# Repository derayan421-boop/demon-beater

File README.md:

# demon-beater
My first hackclub project using KiCad and Fusion360

BOM:
- 3x Cherry MX Switches
- 3x Blank DSA Keycaps
- 1x XIAO RP2040
- 1x SK6812 MINI Led
- 4x M3x16 Bolt
- 4x M3 Heatset

Others(?):
- KMK Firmware
- Top Case.stl
- Bottom Case.stl

Schematic   |   PCB   | Case
:---:|:---:|:---:|
   |      |

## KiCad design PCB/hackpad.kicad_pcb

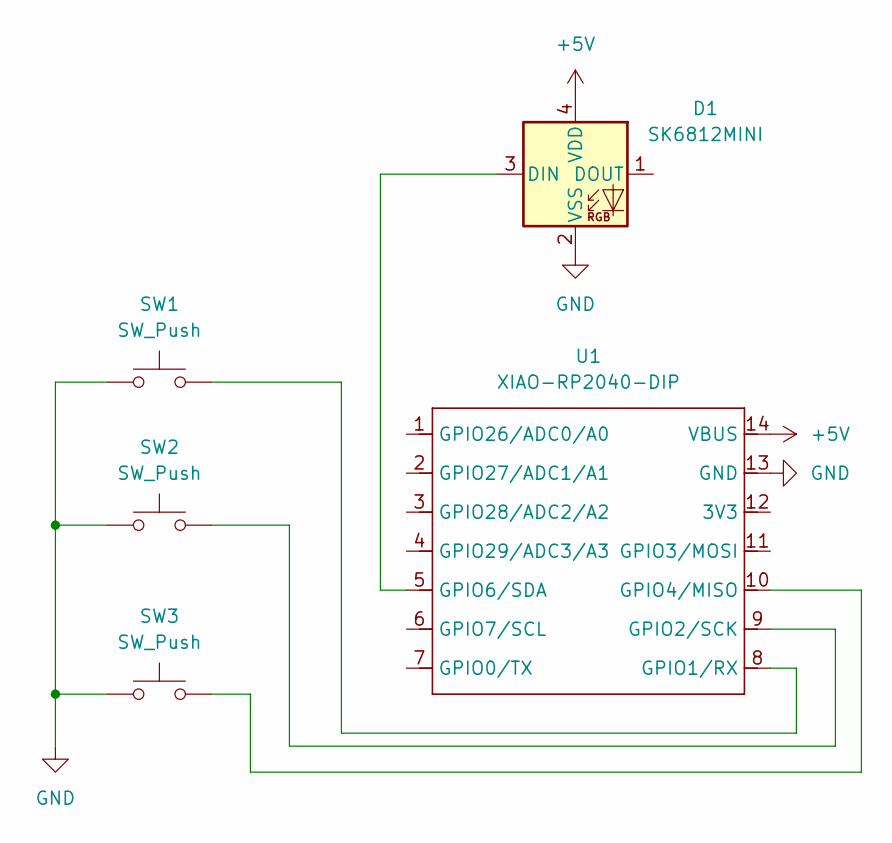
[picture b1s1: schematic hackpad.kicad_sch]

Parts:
D1: SK6812MINI; LED_SK6812MINI_PLCC4_3.5x3.5mm_P1.75mm
SW1, SW2, SW3: SW_Push; SW_Cherry_MX_1.00u_PCB
U1: XIAO-RP2040-DIP

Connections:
+5V: D1.4 (VDD), U1.14 (VBUS)
GND: D1.2 (VSS), SW1.2, SW2.1, SW3.1, U1.13 (GND)
unnamed: D1.3 (DIN), U1.5 (GPIO6/SDA)
unnamed: SW1.1, U1.8 (GPIO1/RX)
unnamed: SW2.2, U1.9 (GPIO2/SCK)
unnamed: SW3.2, U1.10 (GPIO4/MISO)

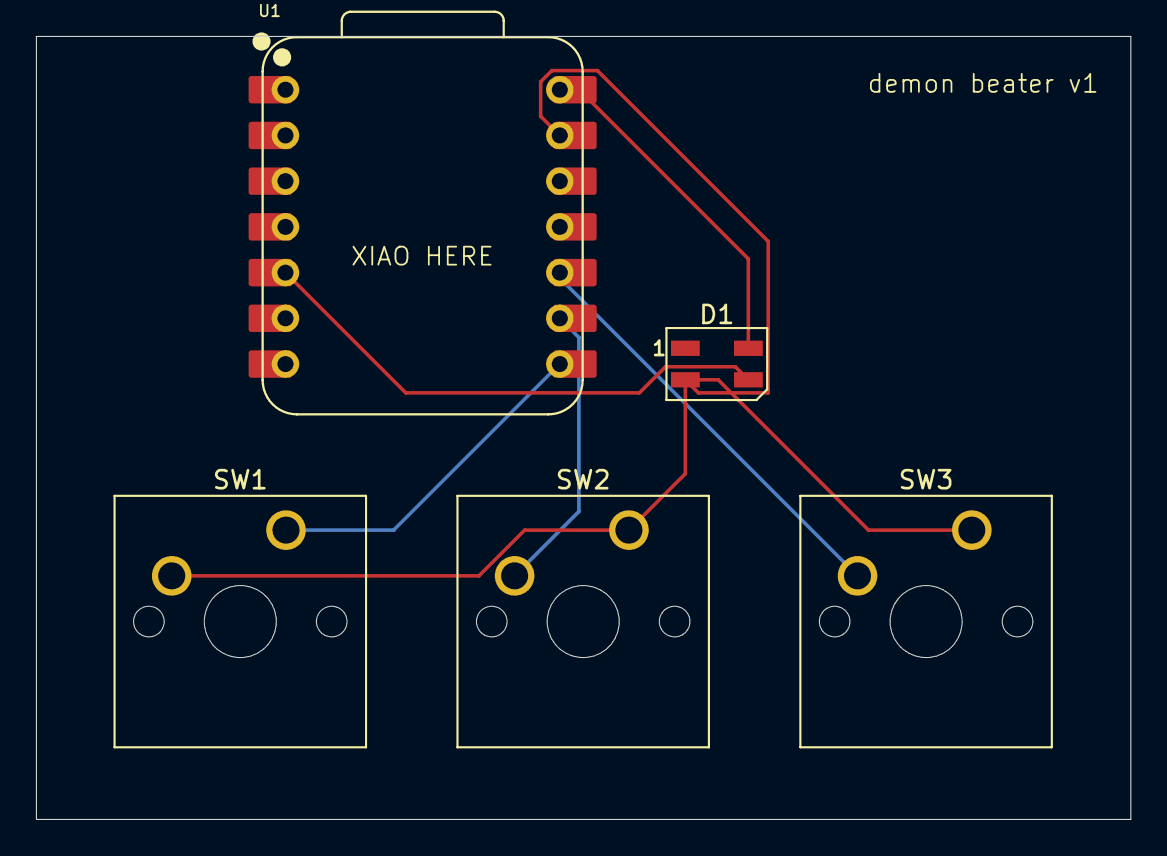
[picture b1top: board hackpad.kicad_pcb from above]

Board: 2 copper layers, 60.8 x 43.5 mm, 5 parts (0 on the bottom side), 6 nets.

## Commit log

2025-11-25 Added PCB
